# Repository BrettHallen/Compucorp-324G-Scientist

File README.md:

# Compucorp 324G Scientist
This information is based on the 324G calculator I have in my possession.  It will be relevant to other 320-series calculators to varying degrees.<br>

This calculator was also sold under other manufacturers' branding:
- Monroe
- Ricoh (as the X822)
- IME
- Sumlock Anita

Other models in the 300-series were:
- 320G Scientist with basic scientific functions
- 322G Scientist with additional programmability (one 80-step program)
- 324G Scientist with additional programmability (two 80-step programs)
- 325 Scientist with additional programmability, printing and cassette tape storage in a much larger case
- 326G Scientist with additional programmability and cassette tape storage
- 327 Scientist with 4x internal memory of the 325
- 340 Statistician with statistics functions
- 342 Statistician with additional programmability (one program)
- 344 Statistician with additional programmability (two programs)
- 354 Surveyor with scientific functions plus programmability (one program)
- 360 Bond Trader with bond trading functions
- 360/65 Bond Trader with additional FED/MUNI switch

The "G" in the model name [indicates](https://www.johnwolff.id.au/calculators/Compucorp/Compucorp320.htm) it could be switched between degrees and gradians/grads/grades/gons via the GRAD/DEG switch.<br>

The calculator is also referred to as the "300 Series Beta Computer".<br>

## Videos
- [Part 1: Power On & Disassembly](https://youtu.be/NjJ8rrLbnn0)
- [Part 2: Display Repair & USB Power](https://youtu.be/J1Y7ZJ_NeyI)
- [Part 3: Programming Lunar Lander](https://youtu.be/Psg4YwRlDQM)

## Power
My 324G came with a 240VAC (Australian) power supply that output an unregulated 11VDC (no load).<br>

It was originally designed to take four D-size NiCd rechargeable batteries.  Probably not a good idea to use non-rechargeable batteries if you are connecting the AC power adaptor.<br>

I have confirmed that the calculator looks to run okay on 5VDC (i.e. USB) consuming just over 1A.  I created a USB-to-2.1mm plug to confirm.

These are the voltages used in the calculator - all voltages except V<sub>SS</sub> are generated by the calculator:
- V<sub>SS</sub>: input voltage from AC charger or batteries (5.5-7V), this is the system's reference voltage and the "logic 1" level
- V<sub>BB</sub>: V<sub>SS</sub> + 3V RAM chip bias voltage
- V<sub>DD</sub>: V<sub>SS</sub> - 7.5V (RAM, ROM, logic)
- V<sub>GG</sub>: V<sub>SS</sub> - 15V (RAM, ROM, logic)
- GND: V<sub>SS</sub> - 5V ("logic 0" level)
- V<sub>BIAS</sub>: -60V (display)
- V<sub>KK</sub>: -120V (display)

## [Principles Of Operation](/Principles_Of_Operation)
Making the text from the Service Manual more easily searchable.

## [Component List](/Components)
Information about the components used in the calculator.

## [Keyboard](/Keyboard)
Information about the keyboard matrix & homebrew replacement keyboard with Cherry MX key switches or 6mm tactile switches - obviously not a direct replacement.

## [KiCad](/KiCad)
KiCad format schematics for the calculator, based on my 324G.<br>

Note that these will likely be incomplete for a long time (forever) depending on what time/interest I have to trace the circuitry.<br>

My main target at the moment is the keyboard and Scan board due to the display issues I have.<br>

### Completion
- Keyboard: 100% complete
- Scan Board: 10% complete
- Processor Board: 95% complete
- Memory Board: 95% complete
- Power Board: 5% complete

## [Manuals](/Manuals)
Any relevant manuals I might come across.

## [Panaplex II](/Panaplex_II_Display)
Information about the Burroughs Panaplex II display used in the calculators as this seems hard-to-come-by.<br>

The particular model is the 16 digit BR 16252 which was used in other devices such as the HP 9815A.<br>

On the 324G, at least, only 15 digits are really used (I think).  The 16th (first on left) is only used for a negative sign (?).<br>

## [Schematics](/Schematics)
Schematics I've generated from KiCad ... I doubt I'll ever find originals.<br>

## [Images](/Images)
Photos of 324G calculator and its internals.

## [Test Harness](/Test_Harness)
Idea I had about creating a test harness: install all the boards onto a special PCB to make testing/troubleshooting easier.  Work in progress.

## [Programs](/Programs)
A programming sheet and sample programs.

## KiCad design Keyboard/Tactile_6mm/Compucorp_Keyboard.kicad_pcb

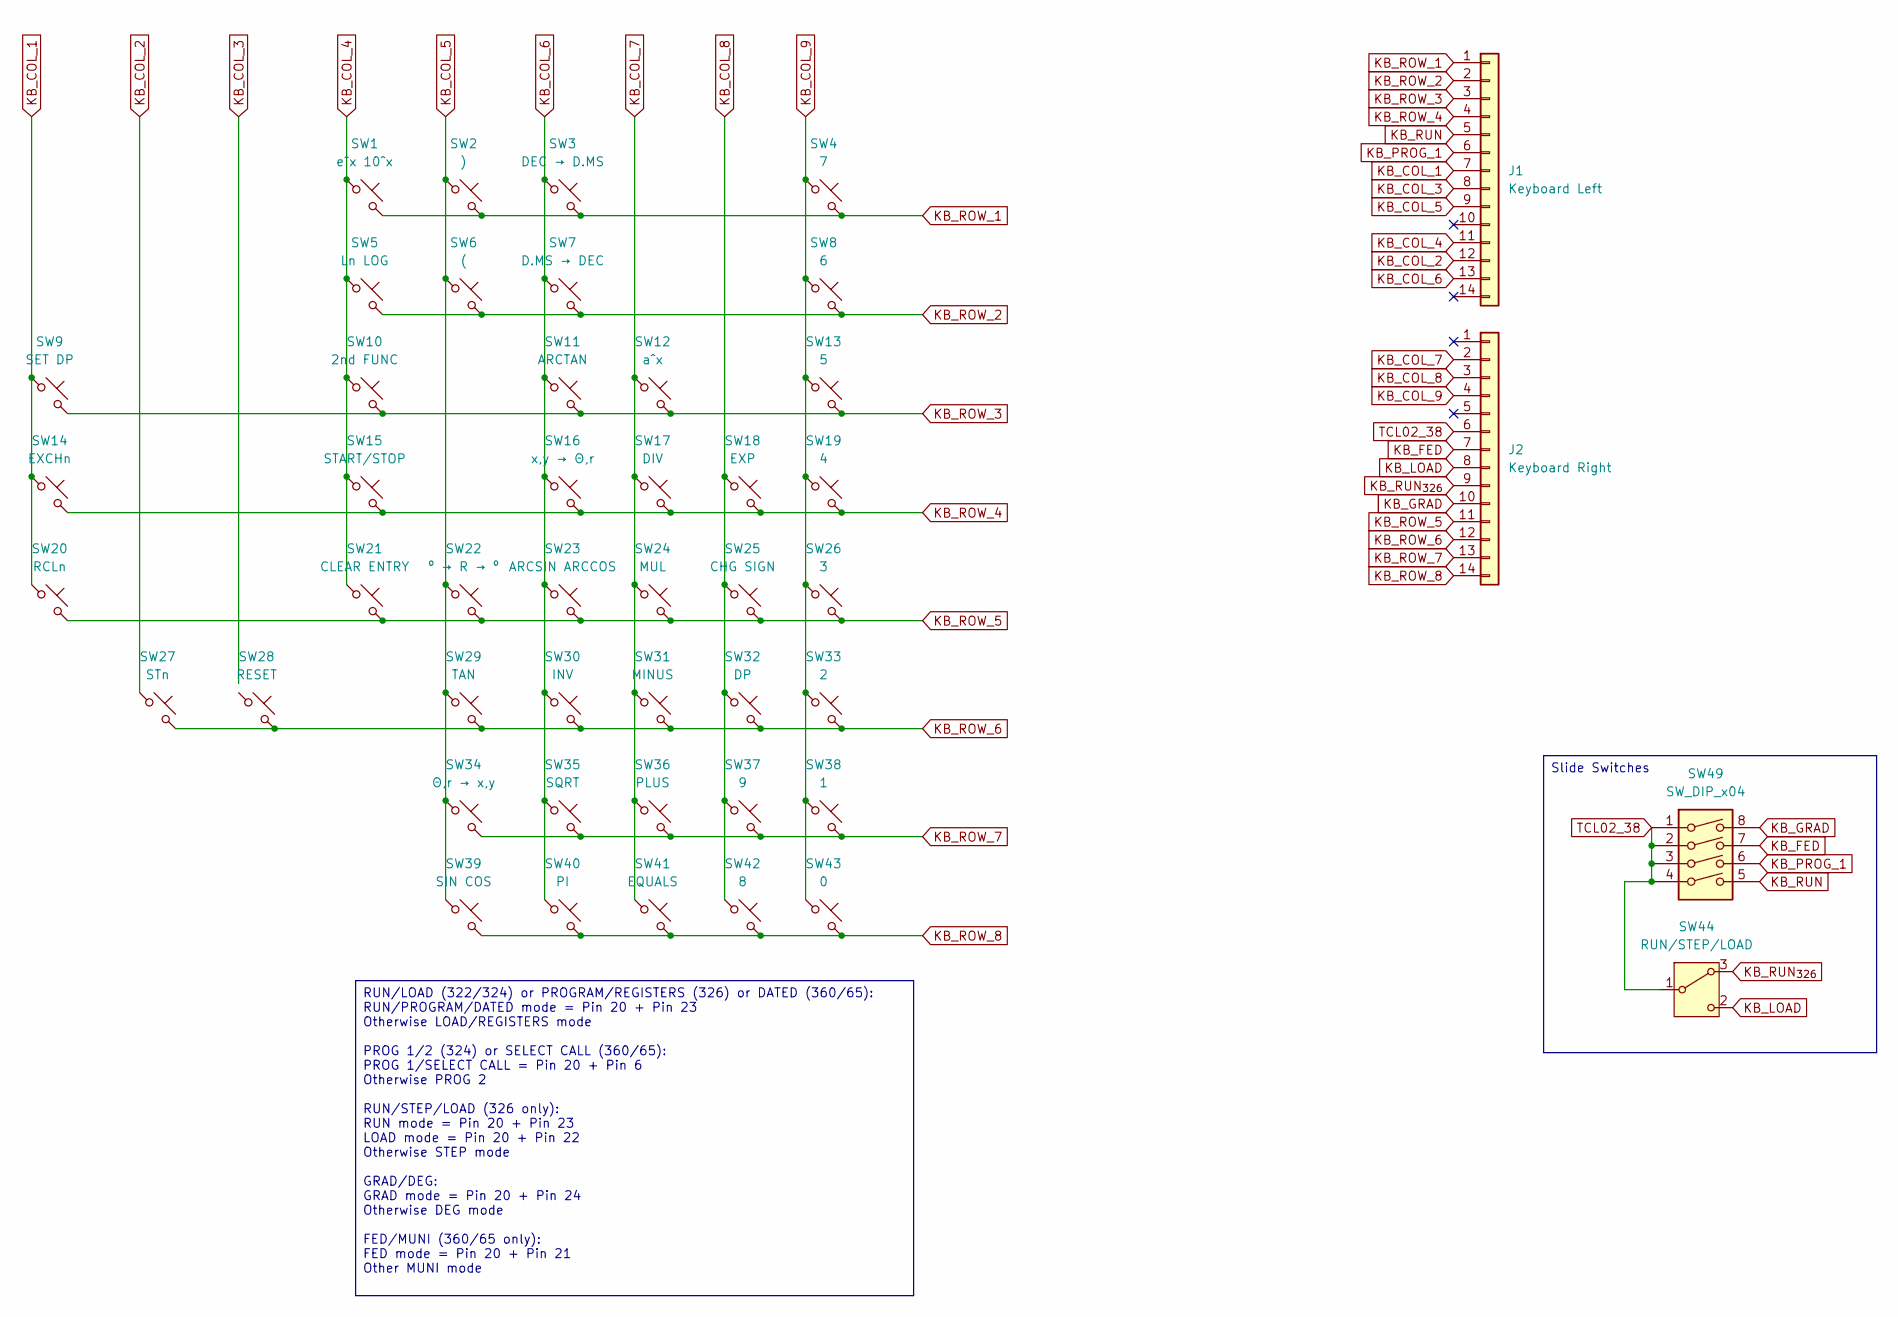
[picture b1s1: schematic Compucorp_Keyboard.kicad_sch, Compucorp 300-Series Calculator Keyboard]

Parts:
J1: Keyboard Left; PinHeader_1x14_P2.54mm_Vertical
J2: Keyboard Right; PinHeader_1x14_P2.54mm_Vertical
SW1: e^x 10^x; SW_PUSH_6mm
SW2: ); SW_PUSH_6mm
SW3: DEC → D.MS; SW_PUSH_6mm
SW4: 7; SW_PUSH_6mm
SW5: Ln LOG; SW_PUSH_6mm
SW6: (; SW_PUSH_6mm
SW7: D.MS → DEC; SW_PUSH_6mm
SW8: 6; SW_PUSH_6mm
SW9: SET DP; SW_PUSH_6mm
SW10: 2nd FUNC; SW_PUSH_6mm
SW11: ARCTAN; SW_PUSH_6mm
SW12: a^x; SW_PUSH_6mm
SW13: 5; SW_PUSH_6mm
SW14: EXCHn; SW_PUSH_6mm
SW15: START/STOP; SW_PUSH_6mm
SW16: x,y → Θ,r; SW_PUSH_6mm
SW17: DIV; SW_PUSH_6mm
SW18: EXP; SW_PUSH_6mm
SW19: 4; SW_PUSH_6mm
SW20: RCLn; SW_PUSH_6mm
SW21: CLEAR ENTRY; SW_PUSH_6mm
SW22: º → R → º; SW_PUSH_6mm
SW23: ARCSIN ARCCOS; SW_PUSH_6mm
SW24: MUL; SW_PUSH_6mm
SW25: CHG SIGN; SW_PUSH_6mm
SW26: 3; SW_PUSH_6mm
SW27: STn; SW_PUSH_6mm
SW28: RESET; SW_PUSH_6mm
SW29: TAN; SW_PUSH_6mm
SW30: INV; SW_PUSH_6mm
SW31: MINUS; SW_PUSH_6mm
SW32: DP; SW_PUSH_6mm
SW33: 2; SW_PUSH_6mm
SW34: Θ,r → x,y; SW_PUSH_6mm
SW35: SQRT; SW_PUSH_6mm
SW36: PLUS; SW_PUSH_6mm
SW37: 9; SW_PUSH_6mm
SW38: 1; SW_PUSH_6mm
SW39: SIN COS; SW_PUSH_6mm
SW40: PI; SW_PUSH_6mm
SW41: EQUALS; SW_PUSH_6mm
SW42: 8; SW_PUSH_6mm
SW43: 0; SW_PUSH_6mm
SW44: RUN/STEP/LOAD; SW_Slide-03_Wuerth-WS-SLTV_10x2.5x6.4_P2.54mm
SW49: SW_DIP_x04; SW_DIP_SPSTx04_Slide_9.78x12.34mm_W7.62mm_P2.54mm

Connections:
KB_COL_1: J1.7, SW9.1, SW14.1, SW20.1
KB_COL_2: J1.12, SW27.1
KB_COL_3: J1.8
KB_COL_4: J1.11, SW1.1, SW5.1, SW10.1, SW15.1, SW21.1
KB_COL_5: J1.9, SW2.1, SW6.1, SW22.1, SW29.1, SW34.1, SW39.1
KB_COL_6: J1.13, SW3.1, SW7.1, SW11.1, SW16.1, SW23.1, SW30.1, SW35.1, SW40.1
KB_COL_7: J2.2, SW12.1, SW17.1, SW24.1, SW31.1, SW36.1, SW41.1
KB_COL_8: J2.3, SW18.1, SW25.1, SW32.1, SW37.1, SW42.1
KB_COL_9: J2.4, SW4.1, SW8.1, SW13.1, SW19.1, SW26.1, SW33.1, SW38.1, SW43.1
KB_FED: J2.7, SW49.7
KB_GRAD: J2.10, SW49.8
KB_LOAD: J2.8, SW44.2 (C)
KB_PROG_1: J1.6, SW49.6
KB_ROW_1: J1.1, SW1.2, SW2.2, SW3.2, SW4.2
KB_ROW_2: J1.2, SW5.2, SW6.2, SW7.2, SW8.2
KB_ROW_3: J1.3, SW9.2, SW10.2, SW11.2, SW12.2, SW13.2
KB_ROW_4: J1.4, SW14.2, SW15.2, SW16.2, SW17.2, SW18.2, SW19.2
KB_ROW_5: J2.11, SW20.2, SW21.2, SW22.2, SW23.2, SW24.2, SW25.2, SW26.2
KB_ROW_6: J2.12, SW27.2, SW28.2, SW29.2, SW30.2, SW31.2, SW32.2, SW33.2
KB_ROW_7: J2.13, SW34.2, SW35.2, SW36.2, SW37.2, SW38.2
KB_ROW_8: J2.14, SW39.2, SW40.2, SW41.2, SW42.2, SW43.2
KB_RUN: J1.5, SW49.5
KB_RUN_{326}: J2.9, SW44.3 (A)
TCL02_38: J2.6, SW44.1 (B), SW49.1, SW49.2, SW49.3, SW49.4

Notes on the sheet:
Slide Switches
RUN/LOAD (322/324) or PROGRAM/REGISTERS (326) or DATED (360/65): RUN/PROGRAM/DATED mode = Pin 20 + Pin 23 Otherwise LOAD/REGISTERS mode PROG 1/2 (324) or SELECT CALL (360/65): PROG 1/SELECT CALL = Pin 20 + Pin 6 Otherwise PROG 2 RUN/STEP/LOAD (326 only): RUN mode = Pin 20 + Pin 23 LOAD mode = Pin 2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

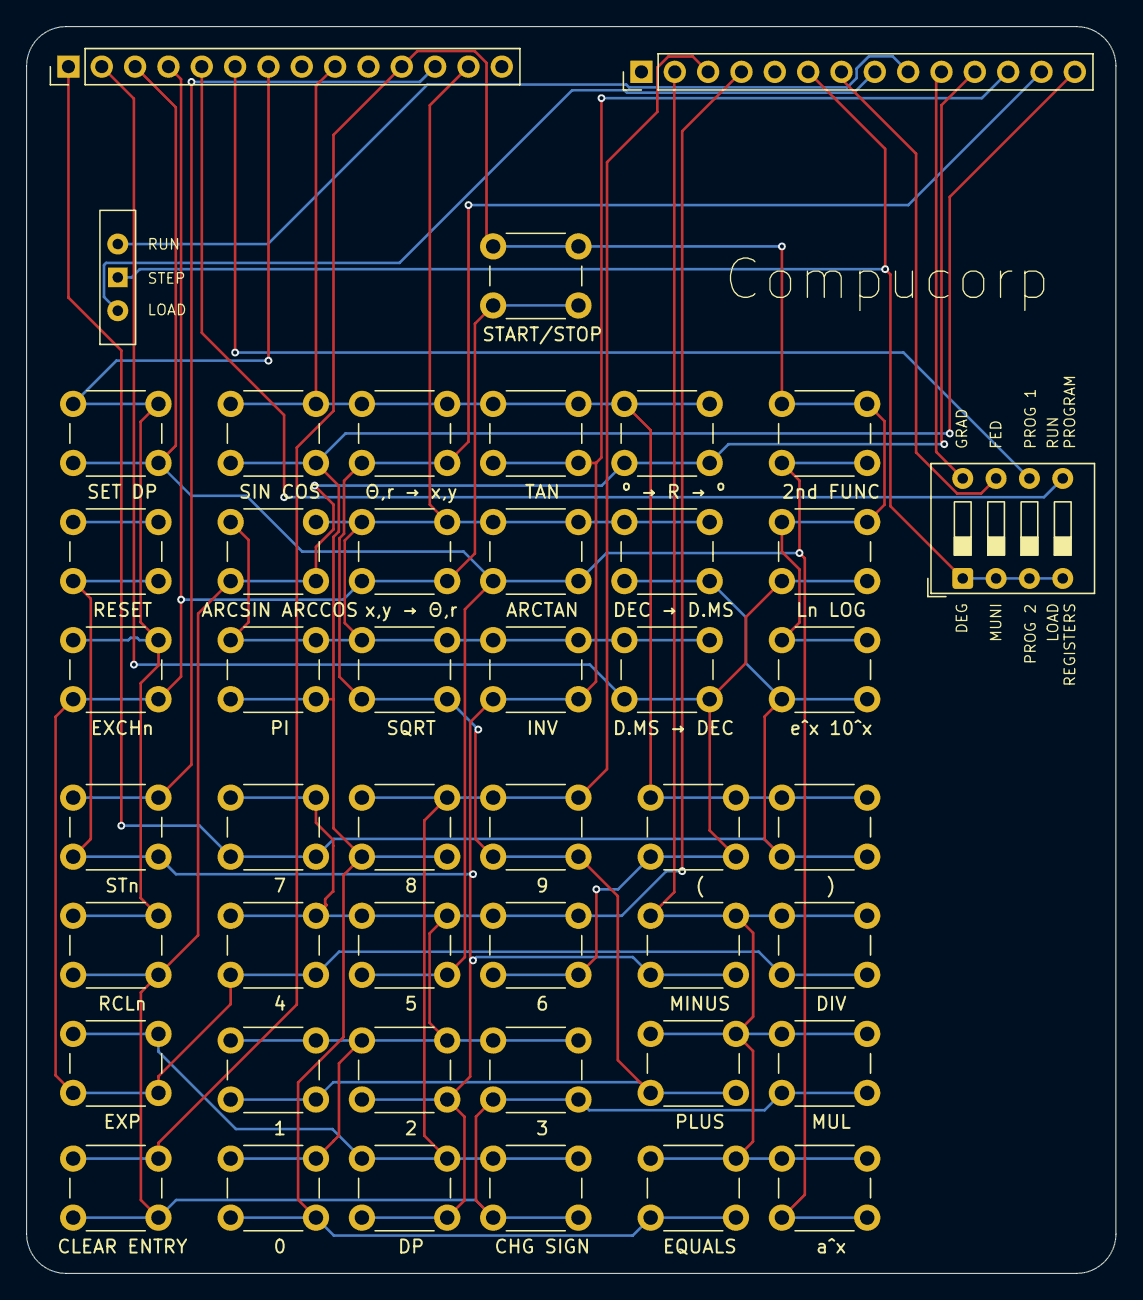
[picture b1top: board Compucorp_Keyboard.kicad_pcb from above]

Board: 2 copper layers, 83.0 x 95.0 mm, 47 parts (0 on the bottom side), 23 nets.

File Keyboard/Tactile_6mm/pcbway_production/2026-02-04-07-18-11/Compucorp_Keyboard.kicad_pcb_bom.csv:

Designator,Quantity,Value,Footprint,Package,MPN,DNP,Mount_Type,Description
J1,1,Keyboard Left,PinHeader_1x14_P2.54mm_Vertical,,,,tht,"Generic connector, single row, 01x14, script generated (kicad-library-utils/schlib/autogen/connector/)"
J2,1,Keyboard Right,PinHeader_1x14_P2.54mm_Vertical,,,,tht,"Generic connector, single row, 01x14, script generated (kicad-library-utils/schlib/autogen/connector/)"
SW1,1,e^x 10^x,SW_PUSH_6mm,,,,tht,"Push button switch, normally open, two pins, 45° tilted"
SW10,1,2nd FUNC,SW_PUSH_6mm,,,,tht,"Push button switch, normally open, two pins, 45° tilted"
SW11,1,ARCTAN,SW_PUSH_6mm,,,,tht,"Push button switch, normally open, two pins, 45° tilted"
SW12,1,a^x,SW_PUSH_6mm,,,,tht,"Push button switch, normally open, two pins, 45° tilted"
SW13,1,5,SW_PUSH_6mm,,,,tht,"Push button switch, normally open, two pins, 45° tilted"
SW14,1,EXCHn,SW_PUSH_6mm,,,,tht,"Push button switch, normally open, two pins, 45° tilted"
SW15,1,START/STOP,SW_PUSH_6mm,,,,tht,"Push button switch, normally open, two pins, 45° tilted"
SW16,1,"x,y → Θ,r",SW_PUSH_6mm,,,,tht,"Push button switch, normally open, two pins, 45° tilted"
SW17,1,DIV,SW_PUSH_6mm,,,,tht,"Push button switch, normally open, two pins, 45° tilted"
SW18,1,EXP,SW_PUSH_6mm,,,,tht,"Push button switch, normally open, two pins, 45° tilted"
SW19,1,4,SW_PUSH_6mm,,,,tht,"Push button switch, normally open, two pins, 45° tilted"
SW2,1,),SW_PUSH_6mm,,,,tht,"Push button switch, normally open, two pins, 45° tilted"
SW20,1,RCLn,SW_PUSH_6mm,,,,tht,"Push button switch, normally open, two pins, 45° tilted"
SW21,1,CLEAR ENTRY,SW_PUSH_6mm,,,,tht,"Push button switch, normally open, two pins, 45° tilted"
SW22,1,º → R → º,SW_PUSH_6mm,,,,tht,"Push button switch, normally open, two pins, 45° tilted"
SW23,1,ARCSIN ARCCOS,SW_PUSH_6mm,,,,tht,"Push button switch, normally open, two pins, 45° tilted"
SW24,1,MUL,SW_PUSH_6mm,,,,tht,"Push button switch, normally open, two pins, 45° tilted"
SW25,1,CHG SIGN,SW_PUSH_6mm,,,,tht,"Push button switch, normally open, two pins, 45° tilted"
SW26,1,3,SW_PUSH_6mm,,,,tht,"Push button switch, normally open, two pins, 45° tilted"
SW27,1,STn,SW_PUSH_6mm,,,,tht,"Push button switch, normally open, two pins, 45° tilted"
SW28,1,RESET,SW_PUSH_6mm,,,,tht,"Push button switch, normally open, two pins, 45° tilted"
SW29,1,TAN,SW_PUSH_6mm,,,,tht,"Push button switch, normally open, two pins, 45° tilted"
SW3,1,DEC → D.MS,SW_PUSH_6mm,,,,tht,"Push button switch, normally open, two pins, 45° tilted"
SW30,1,INV,SW_PUSH_6mm,,,,tht,"Push button switch, normally open, two pins, 45° tilted"
SW31,1,MINUS,SW_PUSH_6mm,,,,tht,"Push button switch, normally open, two pins, 45° tilted"
SW32,1,DP,SW_PUSH_6mm,,,,tht,"Push button switch, normally open, two pins, 45° tilted"
SW33,1,2,SW_PUSH_6mm,,,,tht,"Push button switch, normally open, two pins, 45° tilted"
SW34,1,"Θ,r → x,y",SW_PUSH_6mm,,,,tht,"Push button switch, normally open, two pins, 45° tilted"
SW35,1,SQRT,SW_PUSH_6mm,,,,tht,"Push button switch, normally open, two pins, 45° tilted"
SW36,1,PLUS,SW_PUSH_6mm,,,,tht,"Push button switch, normally open, two pins, 45° tilted"
SW37,1,9,SW_PUSH_6mm,,,,tht,"Push button switch, normally open, two pins, 45° tilted"
SW38,1,1,SW_PUSH_6mm,,,,tht,"Push button switch, normally open, two pins, 45° tilted"
SW39,1,SIN COS,SW_PUSH_6mm,,,,tht,"Push button switch, normally open, two pins, 45° tilted"
SW4,1,7,SW_PUSH_6mm,,,,tht,"Push button switch, normally open, two pins, 45° tilted"
SW40,1,PI,SW_PUSH_6mm,,,,tht,"Push button switch, normally open, two pins, 45° tilted"
SW41,1,EQUALS,SW_PUSH_6mm,,,,tht,"Push button switch, normally open, two pins, 45° tilted"
SW42,1,8,SW_PUSH_6mm,,,,tht,"Push button switch, normally open, two pins, 45° tilted"
SW43,1,0,SW_PUSH_6mm,,,,tht,"Push button switch, normally open, two pins, 45° tilted"
SW44,1,RUN/STEP/LOAD,SW_Slide-03_Wuerth-WS-SLTV_10x2.5x6.4_P2.54mm,,,,tht,"Switch slide, single pole double throw"
SW49,1,SW_DIP_x04,SW_DIP_SPSTx04_Slide_9.78x12.34mm_W7.62mm_P2.54mm,,,,tht,"4x DIP Switch, Single Pole Single Throw (SPST) switch, small symbol"
SW5,1,Ln LOG,SW_PUSH_6mm,,,,tht,"Push button switch, normally open, two pins, 45° tilted"
SW6,1,(,SW_PUSH_6mm,,,,tht,"Push button switch, normally open, two pins, 45° tilted"
SW7,1,D.MS → DEC,SW_PUSH_6mm,,,,tht,"Push button switch, normally open, two pins, 45° tilted"
SW8,1,6,SW_PUSH_6mm,,,,tht,"Push button switch, normally open, two pins, 45° tilted"
SW9,1,SET DP,SW_PUSH_6mm,,,,tht,"Push button switch, normally open, two pins, 45° tilted"

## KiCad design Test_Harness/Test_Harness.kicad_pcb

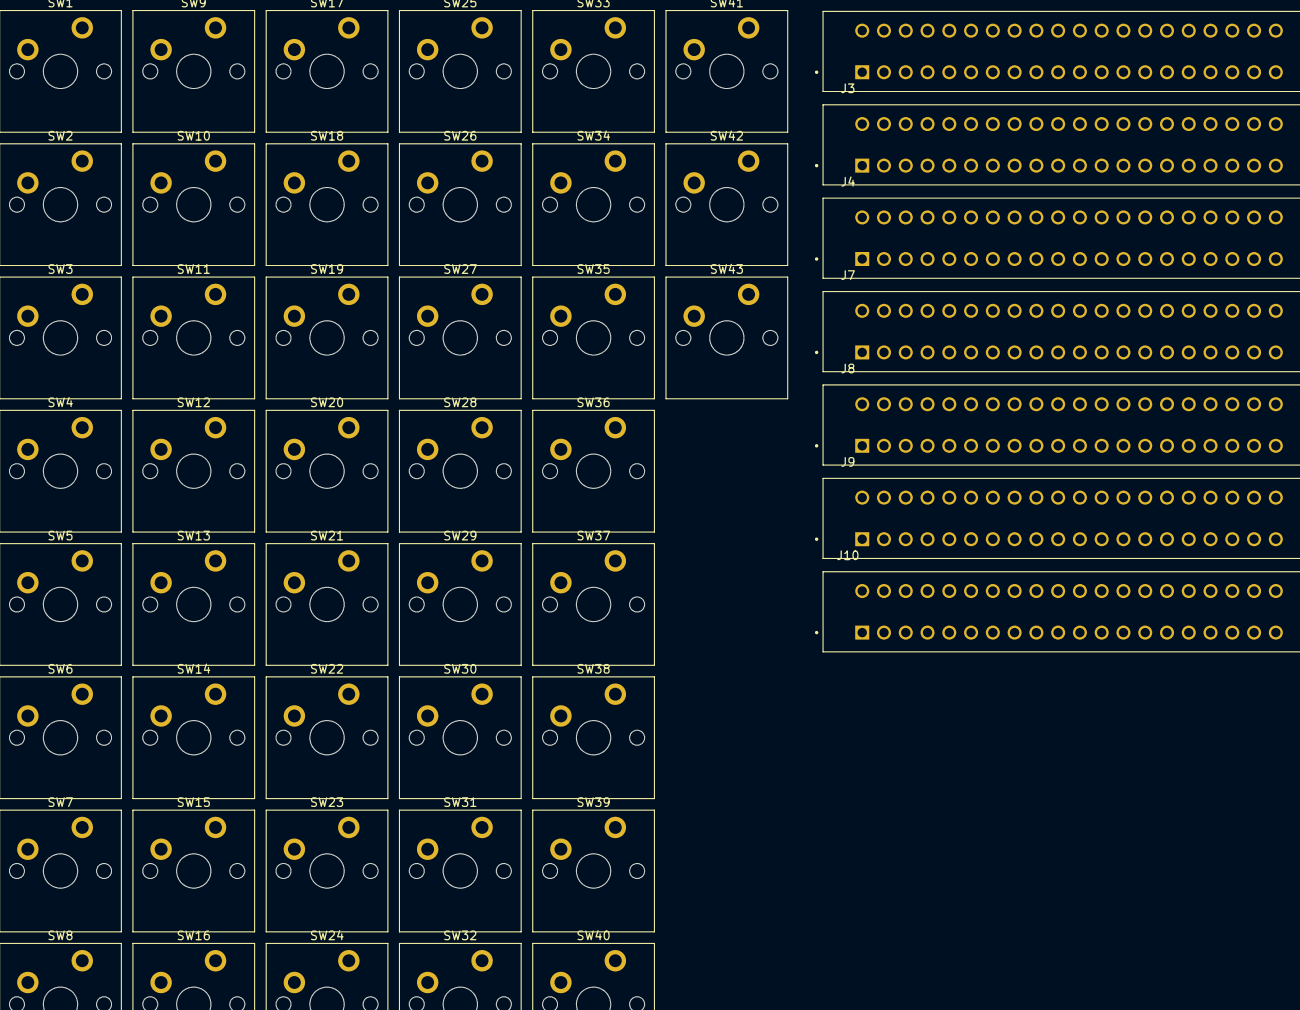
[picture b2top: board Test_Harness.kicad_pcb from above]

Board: 2 copper layers, 50 parts (0 on the bottom side), 15 nets, no tracks yet.

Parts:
J2: Scan 1; TE_5-5530843-4
J3: Processor 1; TE_5-5530843-4
J4: Memory 1; TE_5-5530843-4
J7: Scan 2; TE_5-5530843-4
J8: Processor 2; TE_5-5530843-4
J9: Memory 2; TE_5-5530843-4
J10: Power 2; TE_5-5530843-4
SW1: e^x 10^x; SW_Cherry_MX_PCB_1.00u
SW2: ); SW_Cherry_MX_PCB_1.00u
SW3: DEC → D.MS; SW_Cherry_MX_PCB_1.00u
SW4: 7; SW_Cherry_MX_PCB_1.00u
SW5: Ln LOG; SW_Cherry_MX_PCB_1.00u
SW6: (; SW_Cherry_MX_PCB_1.00u
SW7: D.MS → DEC; SW_Cherry_MX_PCB_1.00u
SW8: 6; SW_Cherry_MX_PCB_1.00u
SW9: SET DP; SW_Cherry_MX_PCB_1.00u
SW10: 2nd FUNC; SW_Cherry_MX_PCB_1.00u
SW11: ARCTAN; SW_Cherry_MX_PCB_1.00u
SW12: a^x; SW_Cherry_MX_PCB_1.00u
SW13: 5; SW_Cherry_MX_PCB_1.00u
SW14: EXCHn; SW_Cherry_MX_PCB_1.00u
SW15: START/STOP; SW_Cherry_MX_PCB_1.00u
SW16: x,y → Θ,r; SW_Cherry_MX_PCB_1.00u
SW17: DIV; SW_Cherry_MX_PCB_1.00u
SW18: EXP; SW_Cherry_MX_PCB_1.00u
SW19: 4; SW_Cherry_MX_PCB_1.00u
SW20: RCLn; SW_Cherry_MX_PCB_1.00u
SW21: CLEAR ENTRY; SW_Cherry_MX_PCB_1.00u
SW22: º → R → º; SW_Cherry_MX_PCB_1.00u
SW23: ARCSIN ARCCOS; SW_Cherry_MX_PCB_1.00u
SW24: MUL; SW_Cherry_MX_PCB_1.00u
SW25: CHG SIGN; SW_Cherry_MX_PCB_1.00u
SW26: 3; SW_Cherry_MX_PCB_1.00u
SW27: STn; SW_Cherry_MX_PCB_1.00u
SW28: RESET; SW_Cherry_MX_PCB_1.00u
SW29: TAN; SW_Cherry_MX_PCB_1.00u
SW30: INV; SW_Cherry_MX_PCB_1.00u
SW31: MINUS; SW_Cherry_MX_PCB_1.00u
SW32: DP; SW_Cherry_MX_PCB_1.00u
SW33: 2; SW_Cherry_MX_PCB_1.00u
SW34: Θ,r → x,y; SW_Cherry_MX_PCB_1.00u
SW35: SQRT; SW_Cherry_MX_PCB_1.00u
SW36: PLUS; SW_Cherry_MX_PCB_1.00u
SW37: 9; SW_Cherry_MX_PCB_1.00u
SW38: 1; SW_Cherry_MX_PCB_1.00u
SW39: SIN COS; SW_Cherry_MX_PCB_1.00u
SW40: PI; SW_Cherry_MX_PCB_1.00u
SW41: EQUALS; SW_Cherry_MX_PCB_1.00u
SW42: 8; SW_Cherry_MX_PCB_1.00u
SW43: 0; SW_Cherry_MX_PCB_1.00u

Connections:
KB Col 1: SW9.1, SW14.1, SW20.1
KB Col 4: SW1.1, SW5.1, SW10.1, SW15.1, SW21.1
KB Col 5: SW2.1, SW6.1, SW22.1, SW29.1, SW34.1, SW39.1
KB Col 6: SW3.1, SW7.1, SW11.1, SW16.1, SW23.1, SW30.1, SW35.1, SW40.1
KB Col 7: SW12.1, SW17.1, SW24.1, SW31.1, SW36.1, SW41.1
KB Col 8: SW18.1, SW25.1, SW32.1, SW37.1, SW42.1
KB Col 9: SW4.1, SW8.1, SW13.1, SW19.1, SW26.1, SW33.1, SW38.1, SW43.1
KB Row 1: SW1.2, SW2.2, SW3.2, SW4.2
KB Row 2: SW5.2, SW6.2, SW7.2, SW8.2
KB Row 3: SW9.2, SW10.2, SW11.2, SW12.2, SW13.2
KB Row 4: SW14.2, SW15.2, SW16.2, SW17.2, SW18.2, SW19.2
KB Row 5: SW20.2, SW21.2, SW22.2, SW23.2, SW24.2, SW25.2, SW26.2
KB Row 6: SW27.2, SW28.2, SW29.2, SW30.2, SW31.2, SW32.2, SW33.2
KB Row 7: SW34.2, SW35.2, SW36.2, SW37.2, SW38.2
KB Row 8: SW39.2, SW40.2, SW41.2, SW42.2, SW43.2

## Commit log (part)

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2026-02-01 Corrected 2N54000
2026-02-01 Added images
2026-02-01 ICs -> Component List
2026-02-01 Updated keyboard schematic
2026-02-01 Updates to schematic
2026-02-01 Started on other board schematics
2026-02-02 Started Memory Board schematic
2026-02-02 Memory board updates
2026-02-02 Development started
2026-02-02 Schematic updates
2026-02-03 Move to Panaplex pinout to schematics folder
2026-02-03 Folder reorg
2026-02-04 Brand new scan
2026-02-05 Memory board 2N4403 images
2026-04-19 Missing pages found
